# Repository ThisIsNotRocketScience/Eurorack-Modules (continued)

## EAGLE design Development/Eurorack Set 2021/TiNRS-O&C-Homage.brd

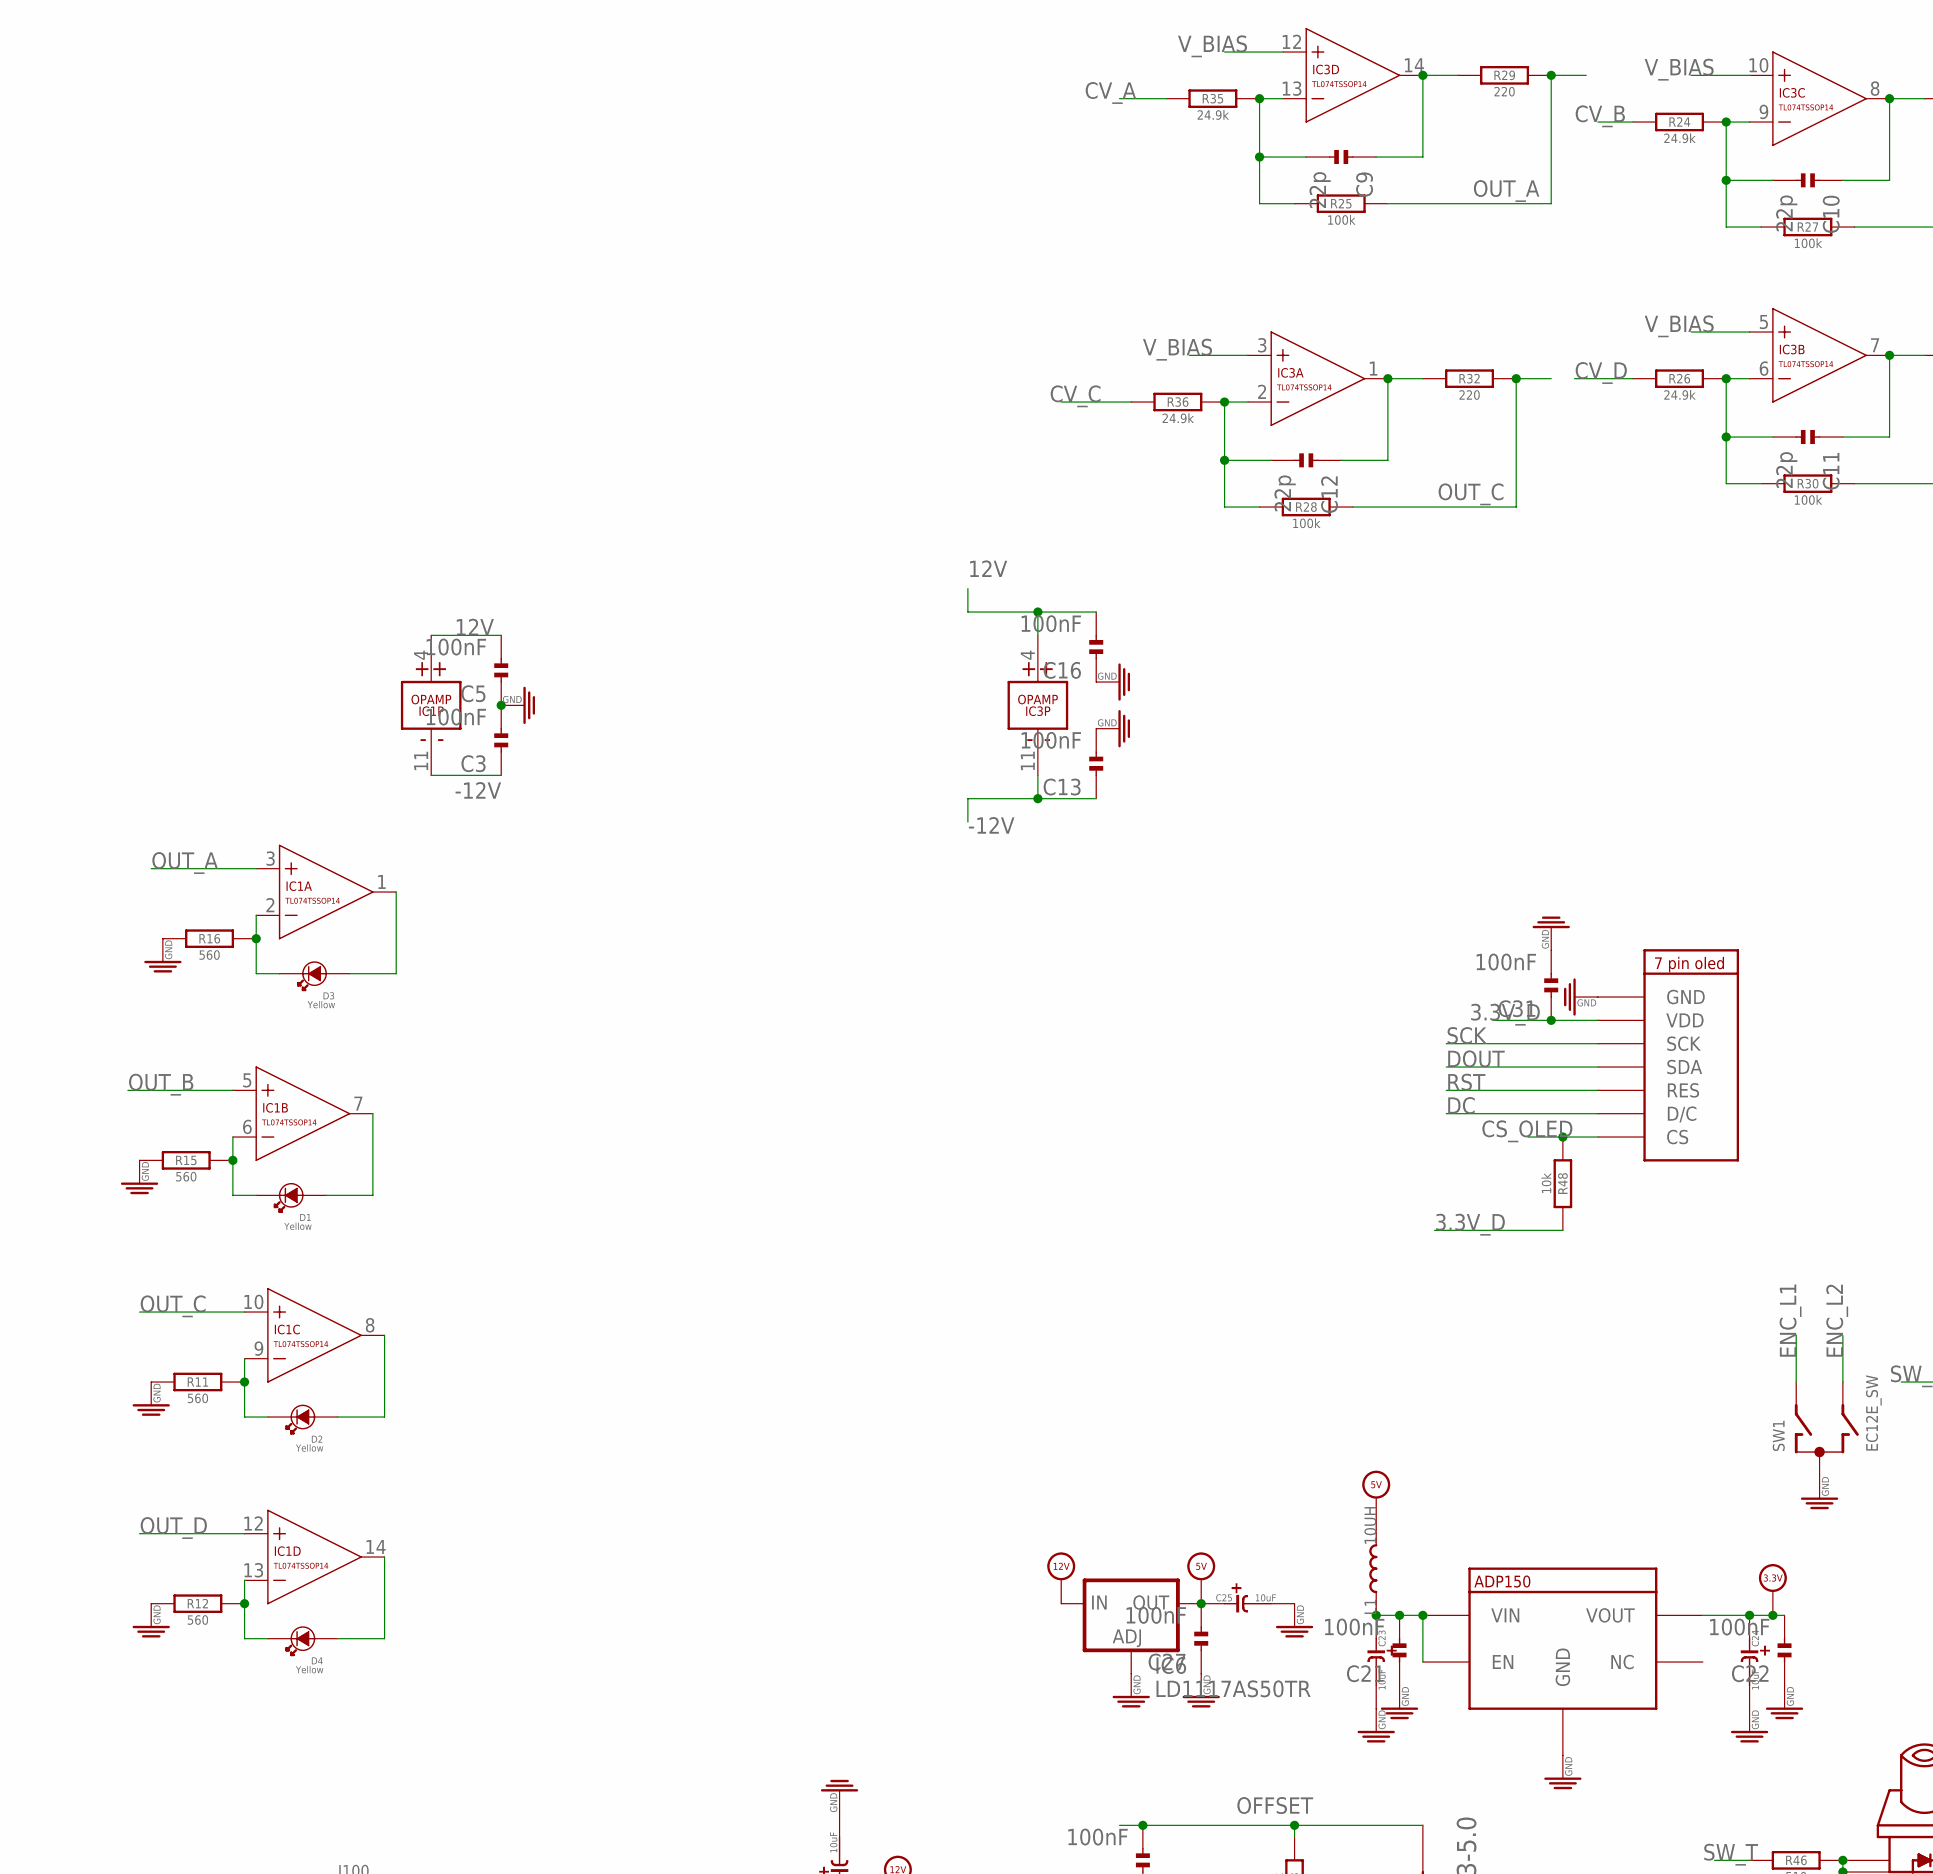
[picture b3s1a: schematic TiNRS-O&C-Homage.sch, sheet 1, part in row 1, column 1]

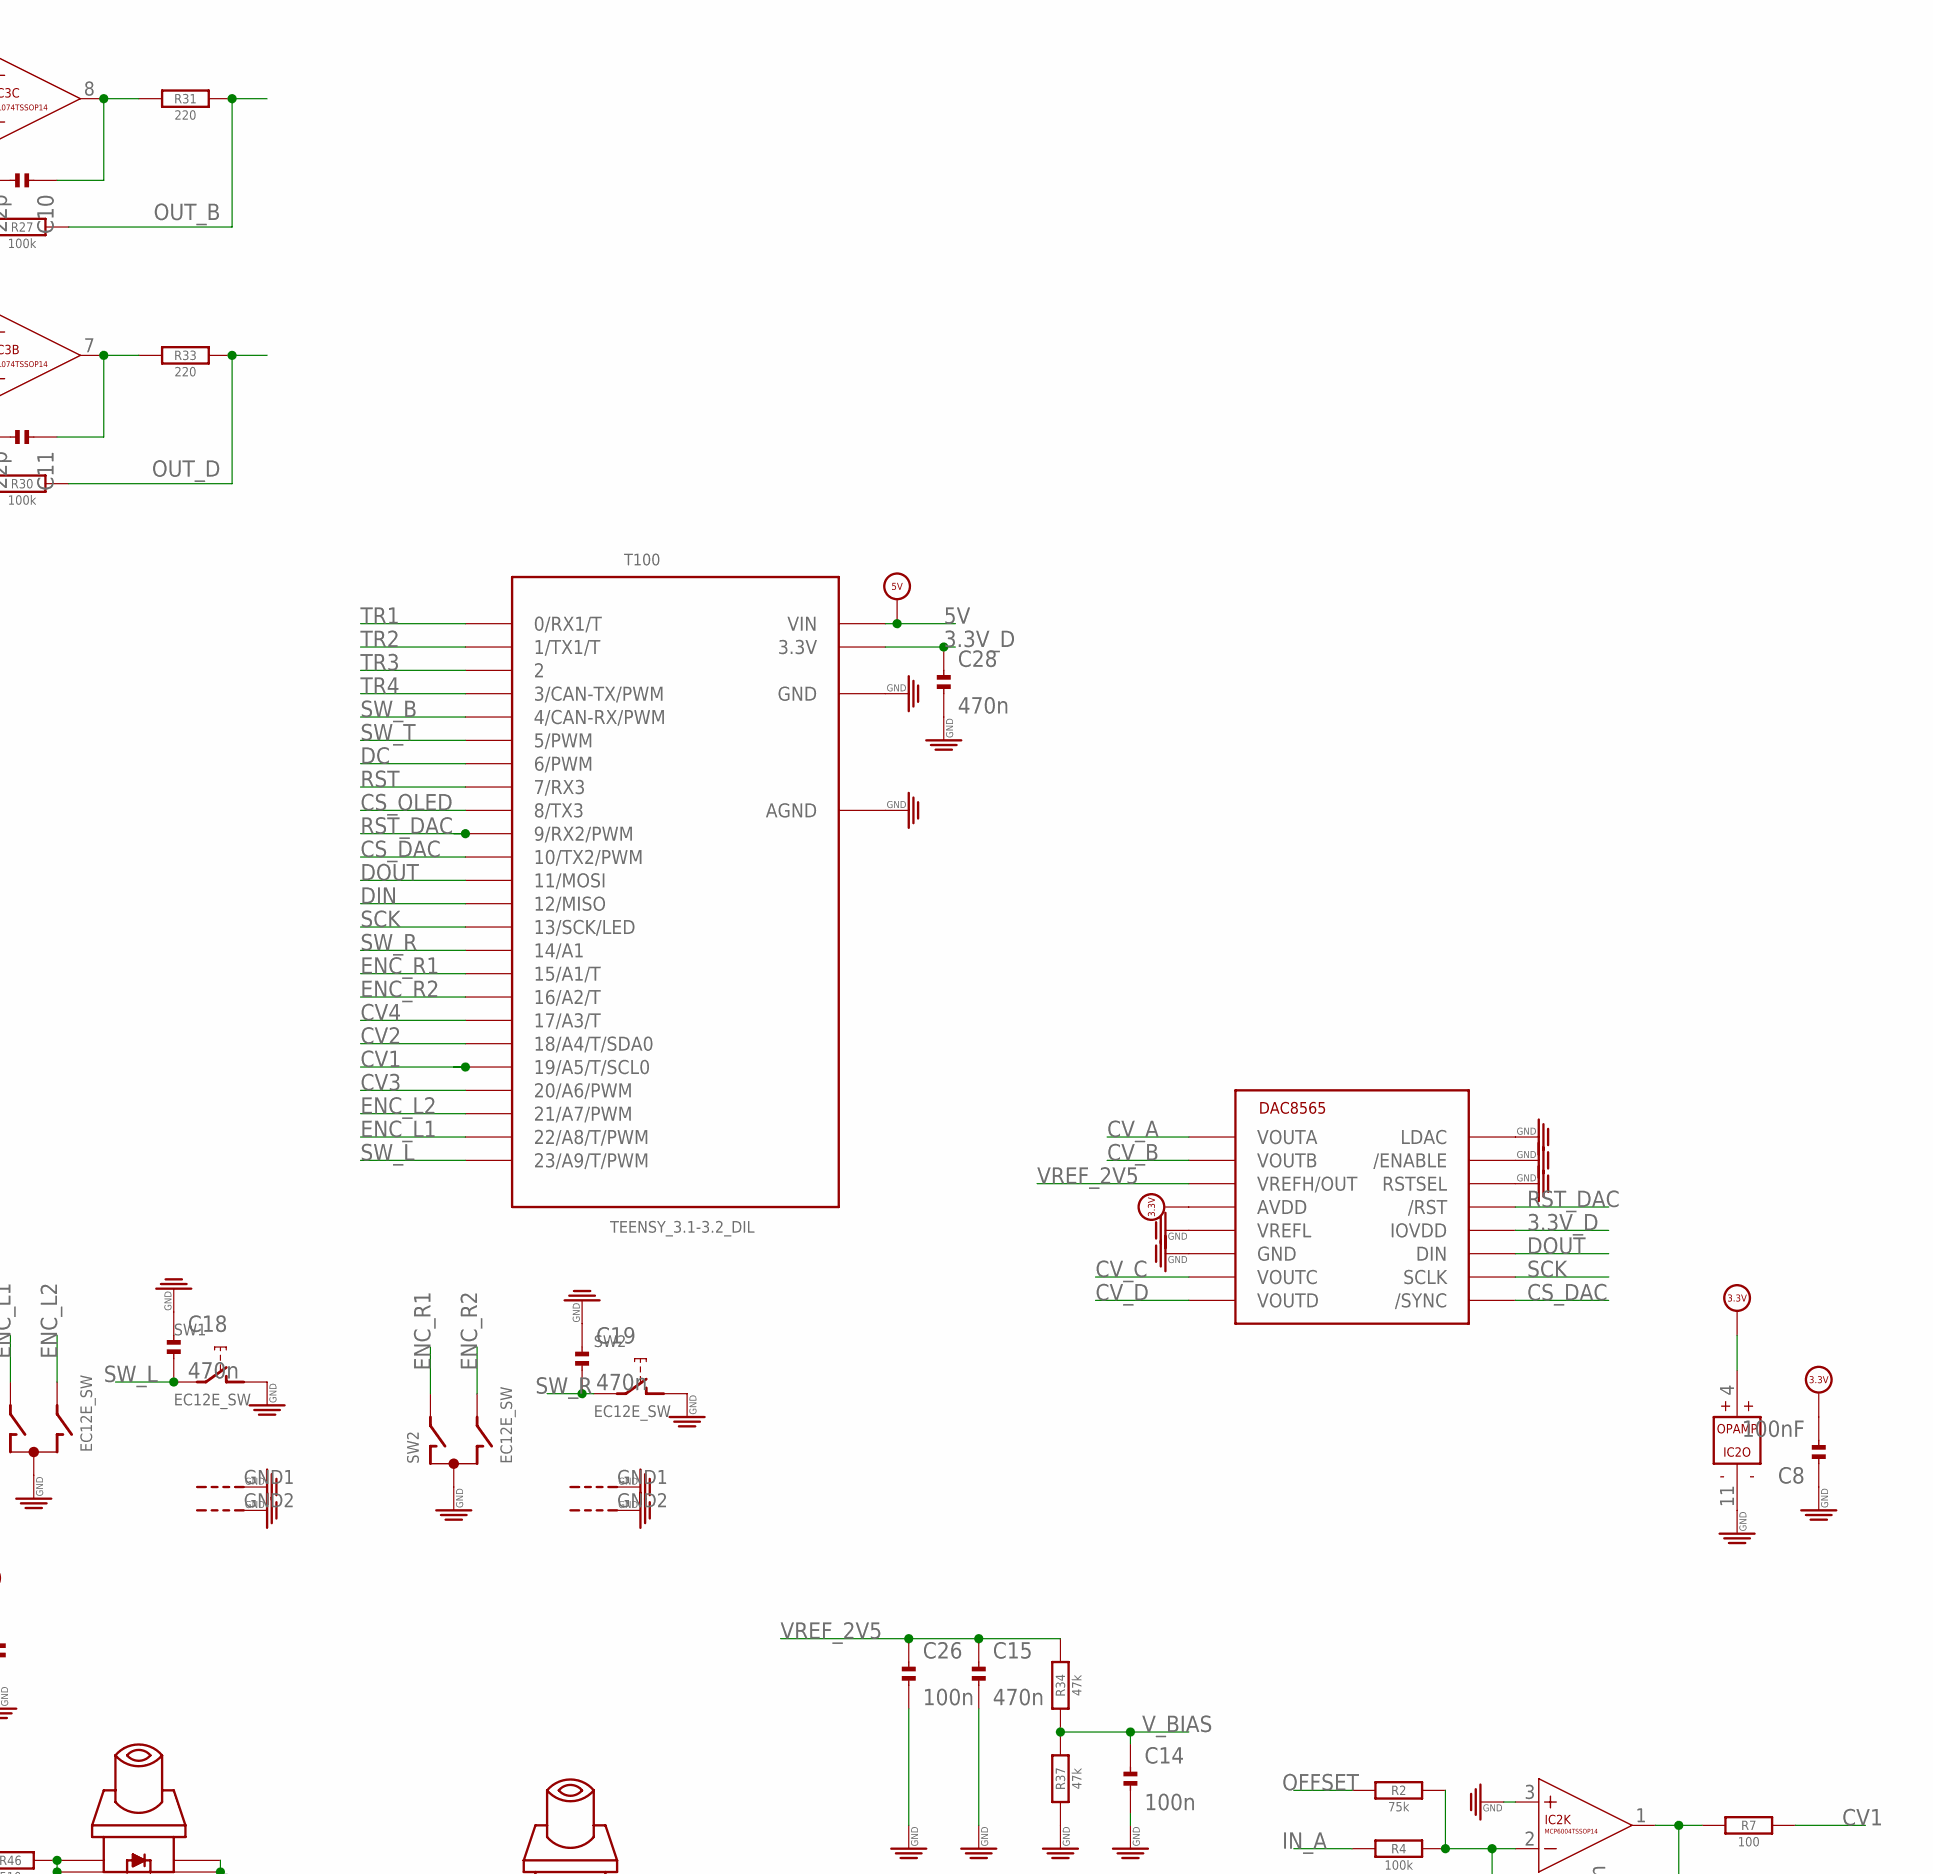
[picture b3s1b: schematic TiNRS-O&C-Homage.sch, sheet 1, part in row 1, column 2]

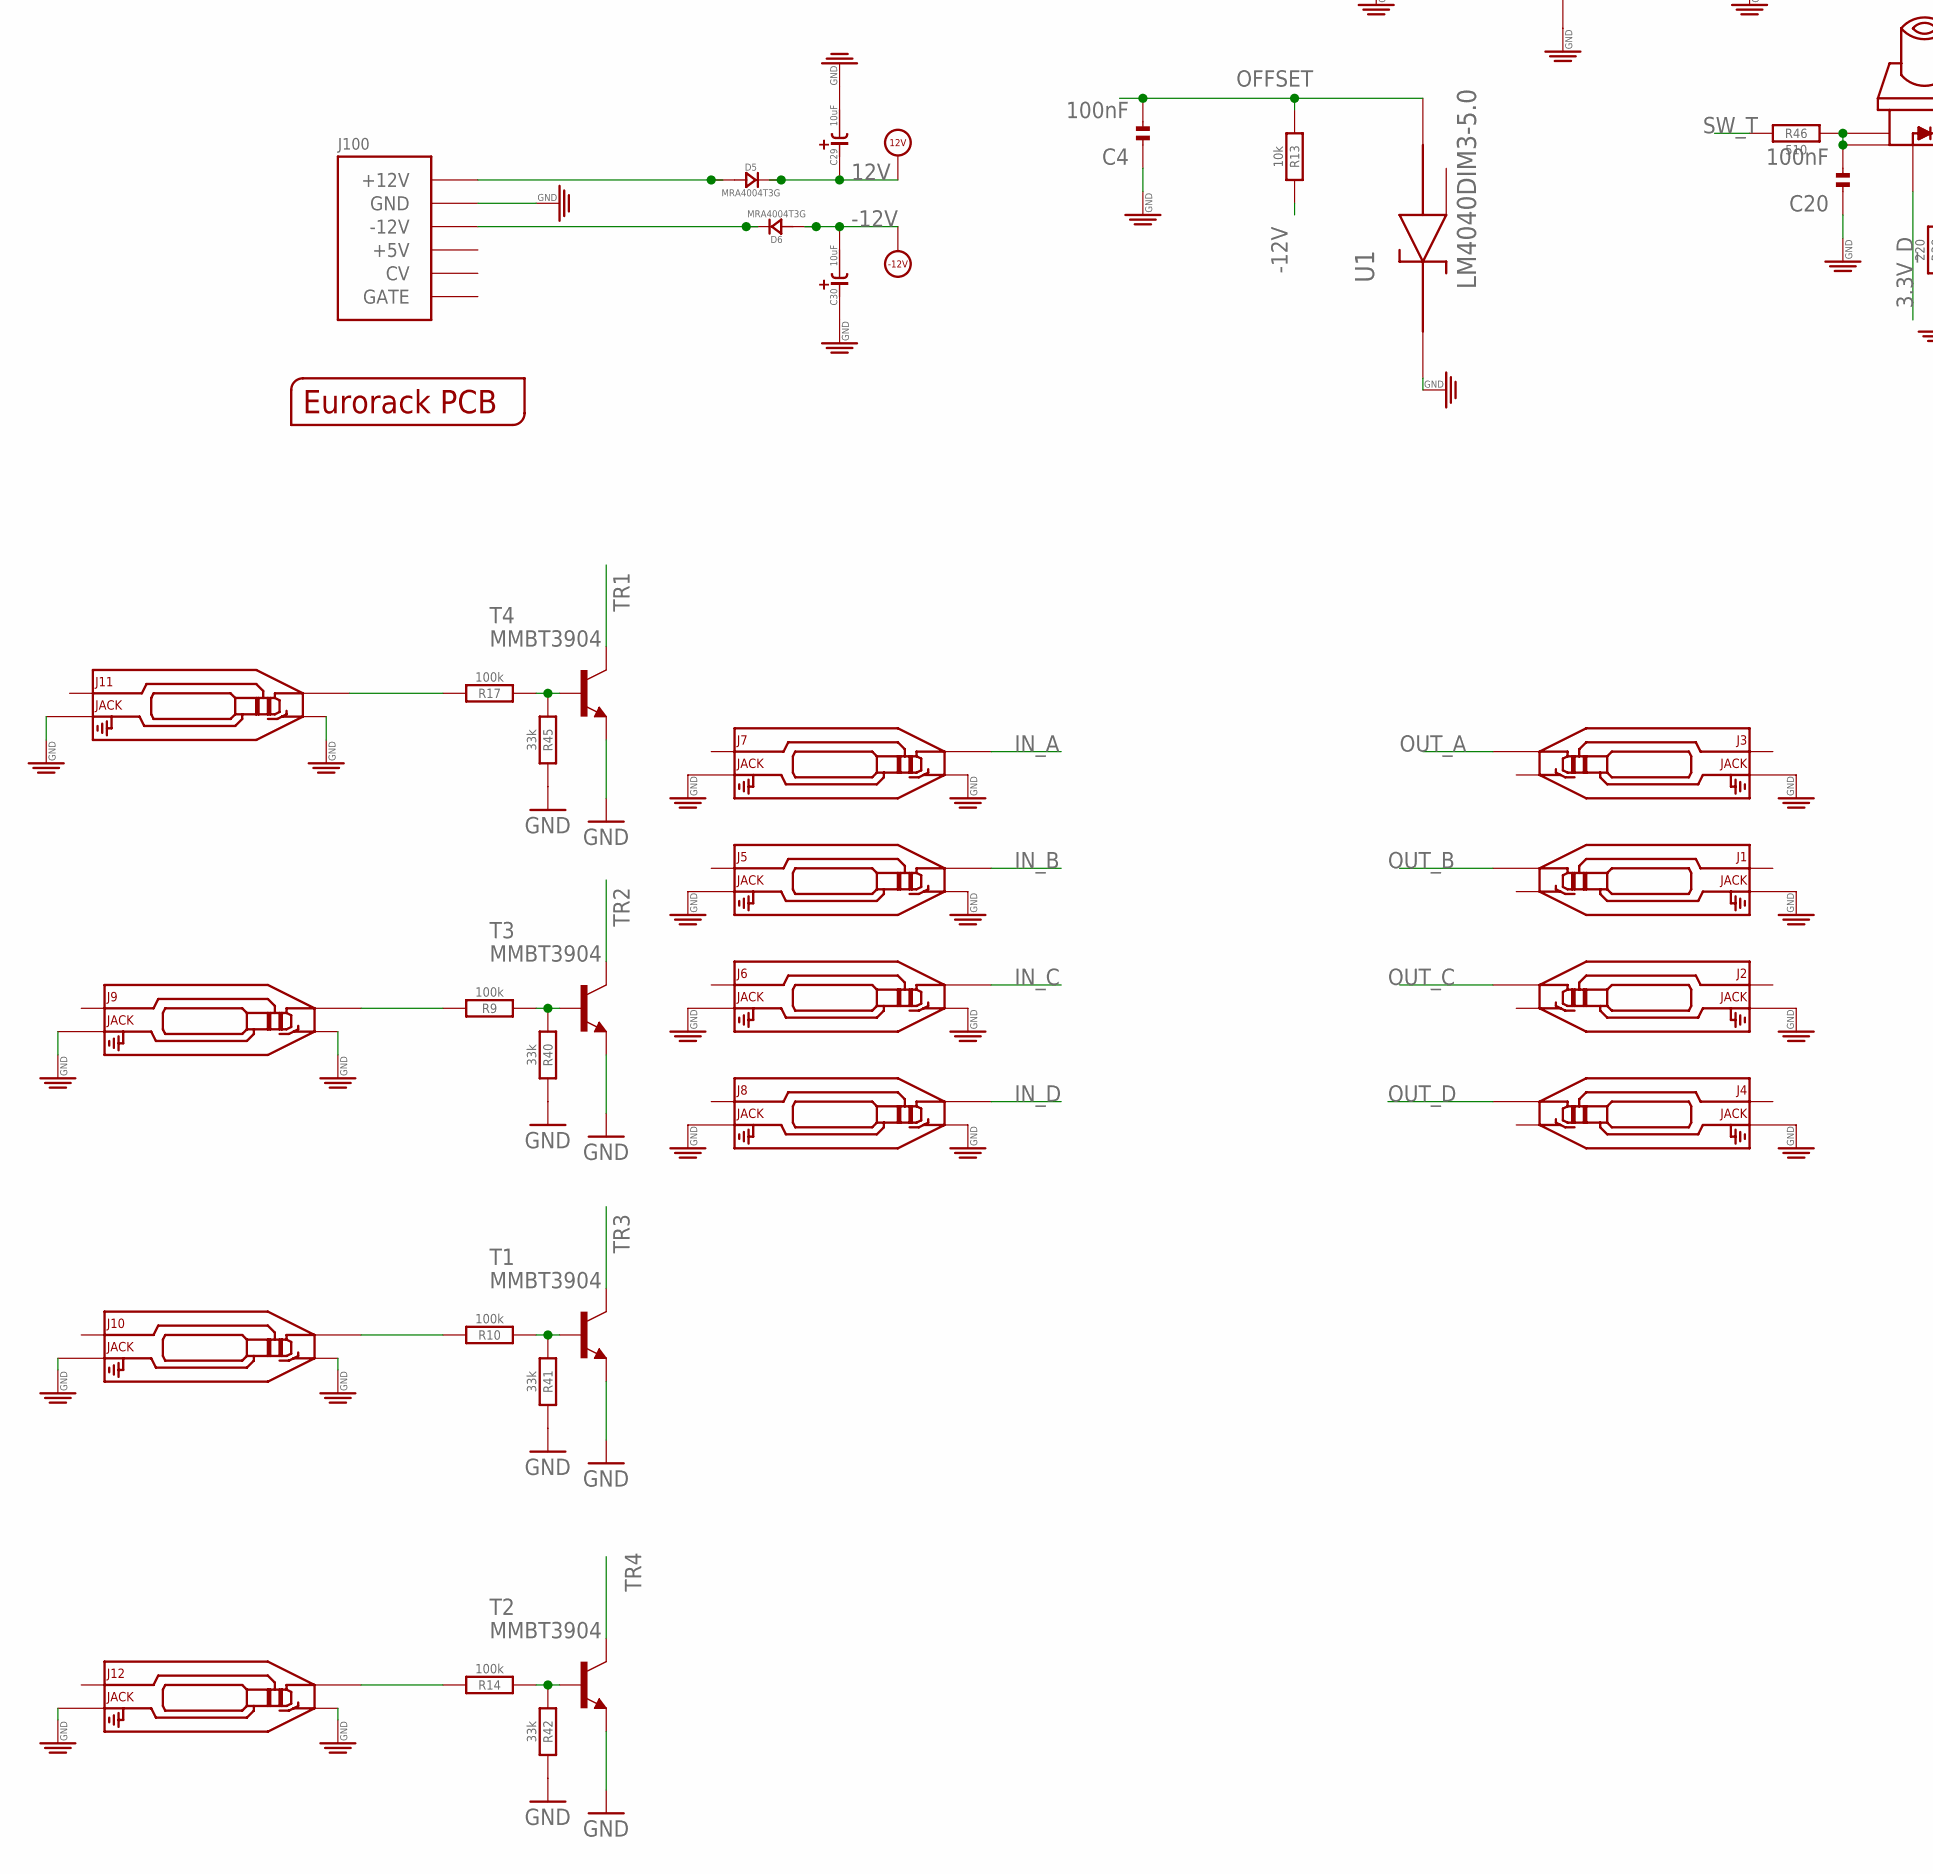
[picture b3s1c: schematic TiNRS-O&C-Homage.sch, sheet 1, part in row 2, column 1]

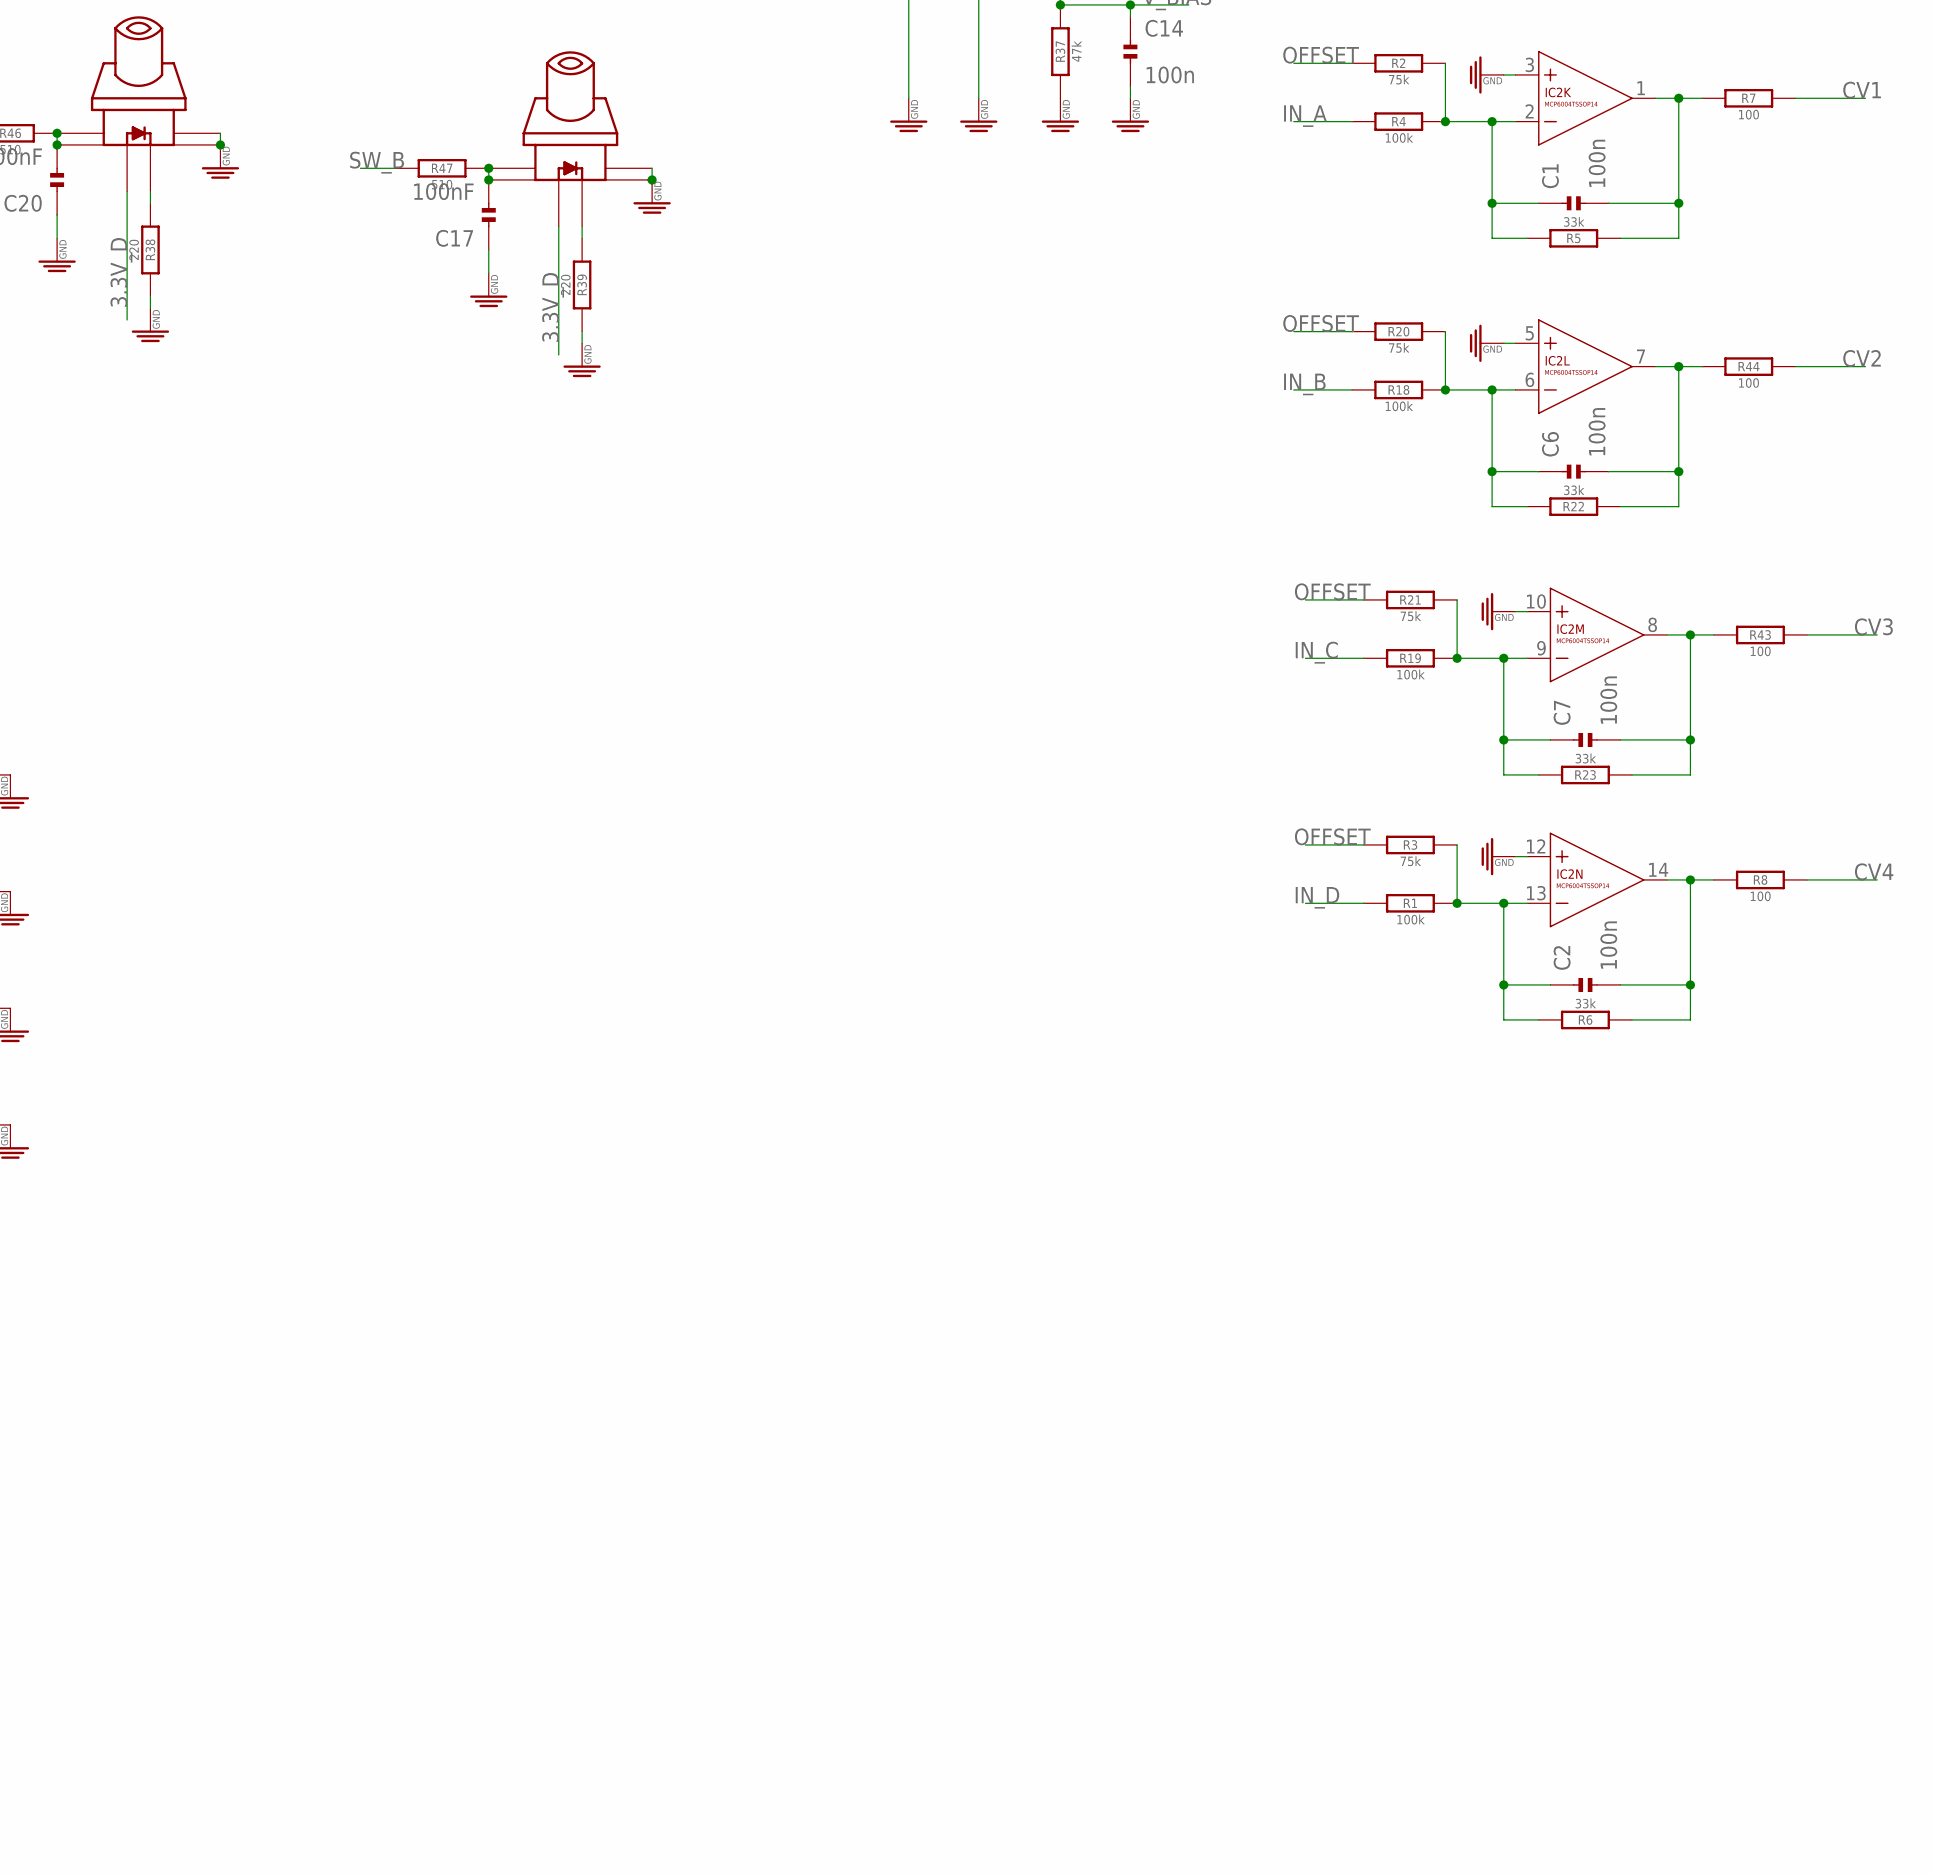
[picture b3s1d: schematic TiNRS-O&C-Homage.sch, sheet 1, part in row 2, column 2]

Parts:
C1, C2, C6, C7, C14, C26: 100n; C0402
C3, C5, C13, C16: 100nF; C0402
C4, C8, C17, C20, C21, C22, C27, C31: 100nF; C0402; MPN 06035C104KAT2A
C9, C10, C11, C12: 22p; C0402
C15, C18, C19, C28: 470n; C0402
C23, C24, C25, C29, C30: 10uF; CASE-A_3216
D1, D2, D3, D4: Yellow; 3MMLED
D5, D6: MRA4004T3G; DO-214AC; MPN US1G-E3/5AT
IC1, IC3: TL074TSSOP14; TSSOP14
IC2: MCP6004TSSOP14; TSSOP14
IC4: ADP1503.3; SOT-23-5
IC5: DAC8565; TSSOP-16
IC6: LD1117AS50TR; SOT223
J1, J2, J3, J4, J5, J6, J7, J8, J9, J10, J11, J12: JACK; 3.5MM-JACK-SWITCH-13MM-NOHOLES-TESTPAD
J100: POWER_SHROUDED_NOTEXT; POWER_16_SHROUDED_NOTEXT
L1: 10UH; L0805
OLED1: 7PIN_SPI_OLED1.3"; 1.3"_7PIN_OLED
PCB1: EURORACK_PCB8HP; EURORACK8HPPCB
R1, R4, R9, R10, R14, R17, R18, R19, R25, R27, R28, R30: 100k; R0402
R2, R3, R20, R21: 75k; R0402
R5, R6, R22, R23, R40, R41, R42, R45: 33k; R0402
R7, R8, R43, R44: 100; R0402
R11, R12, R15, R16: 560; R0402
R13, R48: 10k; R0402
R24, R26, R35, R36: 24.9k; R0402
R29, R31, R32, R33, R38, R39: 220; R0402
R34, R37: 47k; R0402
R46, R47: 510; R0402
S1, S2: SWITCH_W_LED_PB6149L-X-102YELLOW; PB6149L
SW1, SW2: EC12E_SW; ALPS_EC12E_SW
T1, T2, T3, T4: MMBT3904; SOT23-BEC; MPN PMBT3904,215
T100: TEENSY_3.1-3.2_DIL; TEENSY_3.0-3.2&LC_DIL
U1: LM4040DIM3-5.0; SOT95P237X112-3N

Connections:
3.3V: C8.2, C22.2, C24.+ (1), IC2.4 (V+), IC4.5 (VOUT), IC5.P$4 (AVDD)
3.3V_D: C28.1, C31.1, IC5.P$12 (IOVDD), OLED1.P$2 (VDD), R48.1, S1.LEDPOS (POS), S2.LEDPOS (POS), T100.3.3V
5V: C25.+ (1), C27.2, IC6.2 (OUT), IC6.4 (OUT), L1.2, T100.VIN
12V: C5.2, C16.2, C29.+ (1), D5.2 (-), IC1.4 (V+), IC3.4 (V+), IC6.3 (IN)
-12V: C3.1, C13.1, C30.- (2), D6.1 (+), IC1.11 (V-), IC3.11 (V-), R13.1
CS_DAC: IC5.P$9 (/SYNC), T100.10 (10/TX2/PWM)
CS_OLED: OLED1.P$7 (CS), R48.2, T100.8 (8/TX3)
CV1: R7.1, T100.19/A5 (19/A5/T/SCL0)
CV2: R44.1, T100.18/A4 (18/A4/T/SDA0)
CV3: R43.1, T100.20/A6 (20/A6/PWM)
CV4: R8.1, T100.17/A3 (17/A3/T)
CV_A: IC5.P$1 (VOUTA), R35.2
CV_B: IC5.P$2 (VOUTB), R24.2
CV_C: IC5.P$7 (VOUTC), R36.2
CV_D: IC5.P$8 (VOUTD), R26.2
DC: OLED1.P$6 (D/C), T100.6 (6/PWM)
DIN: T100.12 (12/MISO)
DOUT: IC5.P$11 (DIN), OLED1.P$4 (SDA), T100.11 (11/MOSI)
ENC_L1: SW1.A, T100.22/A8 (22/A8/T/PWM)
ENC_L2: SW1.B, T100.21/A7 (21/A7/PWM)
ENC_R1: SW2.A, T100.15/A1 (15/A1/T)
ENC_R2: SW2.B, T100.16/A2 (16/A2/T)
GND: C3.2, C4.1, C5.1, C8.1, C13.2, C14.2, C15.2, C16.1, C17.1, C18.1, C19.1, C20.1, C21.1, C22.1, C23.- (2), C24.- (2), C25.- (2), C26.2, C27.1, C28.2, C29.- (2), C30.+ (1), C31.2, IC2.3 (+IN), IC2.5 (+IN), IC2.10 (+IN), IC2.11 (V-), IC2.12 (+IN), IC4.2 (GND), IC5.P$5 (VREFL), IC5.P$6 (GND), IC5.P$14 (RSTSEL), IC5.P$15 (/ENABLE), IC5.P$16 (LDAC), IC6.1 (ADJ), J1.RING_B@1 (RING), J1.RING_T@3 (RING), J2.RING_B@1 (RING), J2.RING_T@3 (RING), J3.RING_B@1 (RING), J3.RING_T@3 (RING), J4.RING_B@1 (RING), J4.RING_T@3 (RING), J5.RING_B@1 (RING), J5.RING_T@3 (RING), J5.SWITCH_B@1 (SWITCH), J5.SWITCH_T@3 (SWITCH), J6.RING_B@1 (RING), J6.RING_T@3 (RING), J6.SWITCH_B@1 (SWITCH), J6.SWITCH_T@3 (SWITCH), J7.RING_B@1 (RING), J7.RING_T@3 (RING), J7.SWITCH_B@1 (SWITCH), J7.SWITCH_T@3 (SWITCH), J8.RING_B@1 (RING), J8.RING_T@3 (RING), J8.SWITCH_B@1 (SWITCH), J8.SWITCH_T@3 (SWITCH), J9.RING_B@1 (RING), J9.RING_T@3 (RING), J9.SWITCH_B@1 (SWITCH), J9.SWITCH_T@3 (SWITCH), J10.RING_B@1 (RING), J10.RING_T@3 (RING), J10.SWITCH_B@1 (SWITCH), J10.SWITCH_T@3 (SWITCH), J11.RING_B@1 (RING), J11.RING_T@3 (RING), J11.SWITCH_B@1 (SWITCH), J11.SWITCH_T@3 (SWITCH), J12.RING_B@1 (RING), J12.RING_T@3 (RING), J12.SWITCH_B@1 (SWITCH), J12.SWITCH_T@3 (SWITCH), J100.3 (GND), J100.4 (GND), J100.5 (GND), J100.6 (GND), J100.7 (GND), J100.8 (GND), OLED1.P$1 (GND), R11.2, R12.2, R15.2, R16.2, R37.2, R38.1, R39.1, R40.1, R41.1, R42.1, R45.1, S1.3, S1.4, S2.3, S2.4, SW1.C, SW1.D (1), SW1.GND1 (G), SW1.GND2 (G), SW2.C, SW2.D (1), SW2.GND1 (G), SW2.GND2 (G), T1.E, T2.E, T3.E, T4.E, T100.AGND, T100.GND, U1.1 (CATHODE)
IN_A: J7.TIP_B@1 (TIP), J7.TIP_T@3 (TIP), R4.2
IN_B: J5.TIP_B@1 (TIP), J5.TIP_T@3 (TIP), R18.2
IN_C: J6.TIP_B@1 (TIP), J6.TIP_T@3 (TIP), R19.2
IN_D: J8.TIP_B@1 (TIP), J8.TIP_T@3 (TIP), R1.2
unnamed: R38.2, S1.LEDNEG (NEG)
unnamed: R39.2, S2.LEDNEG (NEG)
unnamed: C20.2, R46.1, S1.1, S1.2
unnamed: C17.2, R47.1, S2.1, S2.2
unnamed: R17.2, R45.2, T4.B
unnamed: R9.2, R40.2, T3.B
unnamed: J11.TIP_B@1 (TIP), J11.TIP_T@3 (TIP), R17.1
unnamed: J9.TIP_B@1 (TIP), J9.TIP_T@3 (TIP), R9.1
unnamed: R10.2, R41.2, T1.B
unnamed: J10.TIP_B@1 (TIP), J10.TIP_T@3 (TIP), R10.1
unnamed: R14.2, R42.2, T2.B
unnamed: J12.TIP_B@1 (TIP), J12.TIP_T@3 (TIP), R14.1
unnamed: C12.2, IC3.2 (-IN), R28.2, R36.1
unnamed: C12.1, IC3.1 (OUT), R32.2
unnamed: D1.-, IC1.6 (-IN), R15.1
unnamed: C11.2, IC3.6 (-IN), R26.1, R30.2
unnamed: C11.1, IC3.7 (OUT), R33.2
unnamed: D1.+, IC1.7 (OUT)
unnamed: C10.2, IC3.9 (-IN), R24.1, R27.2
unnamed: C10.1, IC3.8 (OUT), R31.2
unnamed: D2.-, IC1.9 (-IN), R11.1
unnamed: C9.2, IC3.13 (-IN), R25.2, R35.1
unnamed: C9.1, IC3.14 (OUT), R29.2
unnamed: D2.+, IC1.8 (OUT)
unnamed: D4.-, IC1.13 (-IN), R12.1
unnamed: C21.2, C23.+ (1), IC4.1 (VIN), IC4.3 (EN), L1.1
unnamed: D5.1 (+), J100.9 (+12V), J100.10 (+12V)
unnamed: D4.+, IC1.14 (OUT)
unnamed: C6.2, IC2.7 (OUT), R22.2, R44.2
unnamed: C1.2, IC2.1 (OUT), R5.2, R7.2
unnamed: C1.1, IC2.2 (-IN), R2.1, R4.1, R5.1
unnamed: C6.1, IC2.6 (-IN), R18.1, R20.1, R22.1
unnamed: C7.2, IC2.8 (OUT), R23.2, R43.2
unnamed: C7.1, IC2.9 (-IN), R19.1, R21.1, R23.1
unnamed: C2.2, IC2.14 (OUT), R6.2, R8.2
unnamed: C2.1, IC2.13 (-IN), R1.1, R3.1, R6.1
unnamed: D3.-, IC1.2 (-IN), R16.1
unnamed: D6.2 (-), J100.1 (-12V), J100.2 (-12V)
unnamed: D3.+, IC1.1 (OUT)
OFFSET: C4.2, R2.2, R3.2, R13.2, R20.2, R21.2, U1.2 (ANODE)
OUT_A: IC1.3 (+IN), J3.TIP_B@1 (TIP), J3.TIP_T@3 (TIP), R25.1, R29.1
OUT_B: IC1.5 (+IN), J1.TIP_B@1 (TIP), J1.TIP_T@3 (TIP), R27.1, R31.1
OUT_C: IC1.10 (+IN), J2.TIP_B@1 (TIP), J2.TIP_T@3 (TIP), R28.1, R32.1
OUT_D: IC1.12 (+IN), J4.TIP_B@1 (TIP), J4.TIP_T@3 (TIP), R30.1, R33.1
RST: OLED1.P$5 (RES), T100.7 (7/RX3)
RST_DAC: IC5.P$13 (/RST), T100.9 (9/RX2/PWM)
SCK: IC5.P$10 (SCLK), OLED1.P$3 (SCK), T100.13 (13/SCK/LED)
SW_B: R47.2, T100.4 (4/CAN-RX/PWM)
SW_L: C18.2, SW1.E (2), T100.23/A9 (23/A9/T/PWM)
SW_R: C19.2, SW2.E (2), T100.14/A0 (14/A1)
SW_T: R46.2, T100.5 (5/PWM)
TR1: T4.C, T100.0 (0/RX1/T)
TR2: T3.C, T100.1 (1/TX1/T)
TR3: T1.C, T100.2
TR4: T2.C, T100.3 (3/CAN-TX/PWM)
VREF_2V5: C15.1, C26.1, IC5.P$3 (VREFH/OUT), R34.1
V_BIAS: C14.1, IC3.3 (+IN), IC3.5 (+IN), IC3.10 (+IN), IC3.12 (+IN), R34.2, R37.1

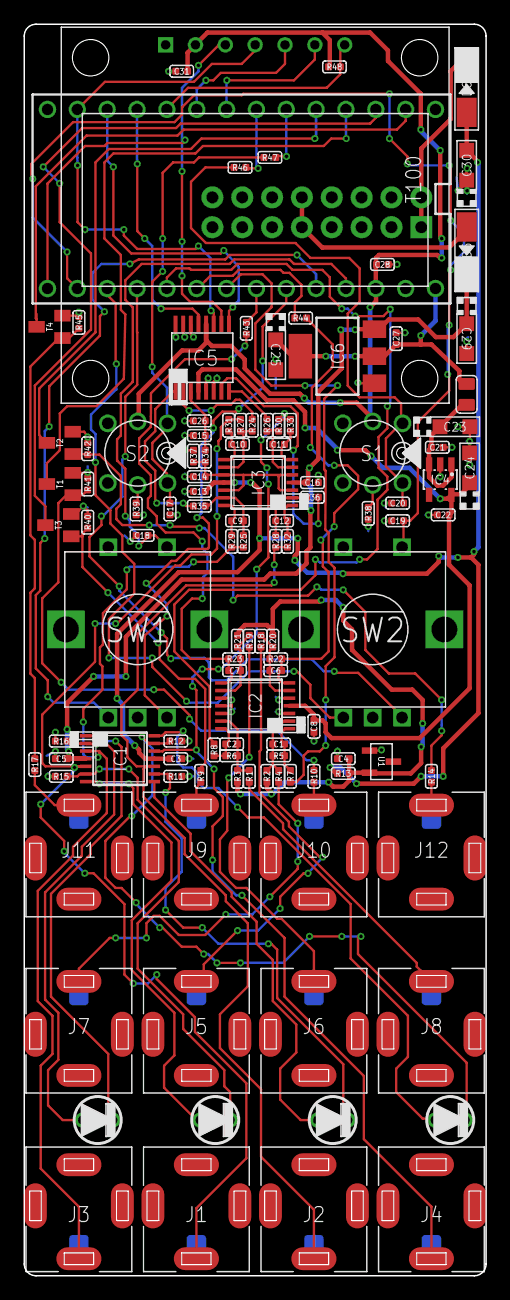
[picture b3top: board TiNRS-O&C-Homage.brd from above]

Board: 2 copper layers, 39.3 x 106.5 mm, 117 parts (1 on the bottom side), 83 nets.
